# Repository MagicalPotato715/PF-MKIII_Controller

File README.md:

****PF-MKIII_Controller****
-----

About: This is the handheld controller for the third-generation of my hexapod project: Pathfinder. This controller features left and right hall effect joysticks - for rotation and movement, respectively. There are also three latch buttons for ON/OFF control of autonomous movement, the hexapod, and the controller itself - alongside numerous miscellaneous status LEDs. Additionally, to communicate with the hexapod, the controller uses an NRF Chip as the main transmitter and an Arduino ESP32 Nano as the MCU. 
---

Why: Pathfinder MK-III itself has an NRF transmitter onboard. Since it's supposed to operate with Inverse Kinematics (live movement), the only options for controls are to either set up a wifi connection with a computer or through a controller. Since the hexapod's MCU, the STM32-f446re, doesn't support wireless code uploading, the only option is through a controller.
---

Bill Of Materials
-----
|Component|Quantity|Model|Lowest Price|Link|
|---|---|---|---|---|
|Dev Board|1|Arduino ESP32 Nano|$11.79|[Link](https://www.aliexpress.com/item/3256807939051766.html?spm=a2g0o.cart.0.0.725738daz9Ksmg&mp=1&pdp_npi=5%40dis%21USD%21USD%2020.26%21USD%2012.56%21%21USD%2012.56%21%21%21%40210156fc17536786169312567e890e%2112000043892831353%21ct%21US%216187826129%21%211%210)|
|Battery|1|3.7v lipo|$5.16|[Link](https://www.aliexpress.com/item/3256808941846105.html?spm=a2g0o.cart.0.0.725738daz9Ksmg&mp=1&pdp_npi=5%40dis%21USD%21USD%205.16%21USD%205.16%21%21USD%205.16%21%21%21%400b1bf20817536788724595407e3676%2112000048014338867%21ct%21US%216187826129%21%211%210)|
|Joysticks|2 (1x5pcs)|09032|$5.3|[Link](https://www.aliexpress.com/item/3256808542713532.html?spm=a2g0o.cart.0.0.725738daz9Ksmg&mp=1&pdp_npi=5%40dis%21USD%21USD%2010.98%21USD%205.38%21%21USD%205.38%21%21%21%400b1bf20817536788724595407e3676%2112000046421716696%21ct%21US%216187826129%21%211%210)|
|NRF Transmitter|1|NRF24L01+|$2.30|[Link](https://www.aliexpress.com/item/3256805495903750.html?spm=a2g0o.productlist.main.2.6555405a81EXOg&algo_pvid=4da61190-12b2-4f13-9f49-e5557cba752b&algo_exp_id=4da61190-12b2-4f13-9f49-e5557cba752b-1&pdp_ext_f=%7B%22order%22%3A%222066%22%2C%22eval%22%3A%221%22%7D&pdp_npi=4%40dis%21USD%211.37%211.37%21%21%219.77%219.77%21%40212a6e2917536789864826848eb8be%2112000033996194288%21sea%21US%216187826129%21X&curPageLogUid=BgwmNtiZJQbL&utparam-url=scene%3Asearch%7Cquery_from%3A)|
|Latch Button|3 (1x10pcs)|6Pin Push Tactile|$1.29|[Link](https://www.aliexpress.com/item/2255800510764155.html?spm=a2g0o.cart.0.0.79d738daWxrOFF&mp=1&pdp_npi=5%40dis%21USD%21USD%201.29%21USD%201.29%21%21USD%201.29%21%21%21%40212a70c117536791531033590e52c9%2110000006101802626%21ct%21US%216187826129%21%211%210)|
|OLED Screen|1|SSD1306|$2.05|[Link](https://www.aliexpress.com/item/3256805954920554.html?spm=a2g0o.cart.0.0.79d738daWxrOFF&mp=1&pdp_npi=5%40dis%21USD%21USD%202.05%21USD%202.05%21%21USD%202.05%21%21%21%40212a70c117536791531033590e52c9%2112000035944225408%21ct%21US%216187826129%21%211%210)|
|Button|1|PBS-33B-G-X|$3.19|[Link](https://www.aliexpress.com/item/3256807265866776.html?spm=a2g0o.cart.0.0.79d738daWxrOFF&mp=1&pdp_npi=5%40dis%21USD%21USD%203.19%21USD%203.19%21%21USD%203.19%21%21%21%40212a70c117536791531033590e52c9%2112000040814174970%21ct%21US%216187826129%21%211%210)|
|RGB LED|2 (1x50pcs)|Common Cathode|$2.40|[Link](https://www.aliexpress.com/item/3256807678016250.html?spm=a2g0o.cart.0.0.79d738daWxrOFF&mp=1&pdp_npi=5%40dis%21USD%21USD%203.63%21USD%202.40%21%21USD%202.40%21%21%21%40212a70c117536791531033590e52c9%2112000042596159855%21ct%21US%216187826129%21%211%210)|
|Resistor Pack|1|510R, 44.7KR|$5.61|[Link](https://www.aliexpress.com/item/3256807883956541.html?spm=a2g0o.productlist.main.2.143211f2uS3ioA&algo_pvid=a85366f6-d296-4a62-9b70-adf952553cac&algo_exp_id=a85366f6-d296-4a62-9b70-adf952553cac-1&pdp_ext_f=%7B%22order%22%3A%22258%22%2C%22eval%22%3A%221%22%7D&pdp_npi=4%40dis%21USD%218.38%215.61%21%21%2159.73%2140.00%21%40213ba0c517536799111818556ea347%2112000043532036113%21sea%21US%216187826129%21X&curPageLogUid=7XvXStSYsJtD&utparam-url=scene%3Asearch%7Cquery_from%3A#nav-specification)|
|10uF Capacitor|1|0805W106K250CC|$0.6|[Link](https://www.aliexpress.com/item/1626652703.html?spm=a2g0o.productlist.main.1.48fb6316RMeZBk&algo_pvid=e693861e-0391-4f51-8de6-32cd16f941e8&algo_exp_id=e693861e-0391-4f51-8de6-32cd16f941e8-0&pdp_ext_f=%7B%22order%22%3A%22290%22%2C%22eval%22%3A%221%22%7D&pdp_npi=4%40dis%21USD%210.60%210.60%21%21%210.60%210.60%21%402102f22c17525900041745529e7ed1%2165044401121%21sea%21TW%216187826129%21ABX&curPageLogUid=cULtsx9Twjzu&utparam-url=scene%3Asearch%7Cquery_from%3A)|
|0.1uF Capacitor|2 (1x100pcs)|0603B104K250SD|$0.95|[Link](https://www.aliexpress.com/item/1005003512666695.html?spm=a2g0o.productlist.main.2.bb674964zgo3zW&aem_p4p_detail=202507151825544677393916540000689187&algo_pvid=30290dc5-6cab-4384-9250-c0f4dd7da1ce&algo_exp_id=30290dc5-6cab-4384-9250-c0f4dd7da1ce-1&pdp_ext_f=%7B%22order%22%3A%2266%22%2C%22eval%22%3A%221%22%7D&pdp_npi=4%40dis%21USD%210.95%210.95%21%21%210.95%210.95%21%400b1bf20a17526291538932348e9ac6%2112000026122537038%21sea%21TW%216187826129%21ABX&curPageLogUid=3zYrgz8WWygI&utparam-url=scene%3Asearch%7Cquery_from%3A&search_p4p_id=202507151825544677393916540000689187_1)|
|LED|2 (1x50pcs)|Green|$1.49|[Link](https://www.aliexpress.com/item/3256806082739727.html?spm=a2g0o.productlist.main.20.58265d61KYx3M3&algo_pvid=2888cd1a-db46-49cb-bcd1-dad9a1187035&algo_exp_id=2888cd1a-db46-49cb-bcd1-dad9a1187035-17&pdp_ext_f=%7B%22order%22%3A%22253%22%2C%22eval%22%3A%221%22%7D&pdp_npi=4%40dis%21USD%212.66%211.76%21%21%2118.96%2112.51%21%402102f22c17536801089633238e9268%2112000036543284014%21sea%21US%216187826129%21X&curPageLogUid=MgZMrUkmbKE4&utparam-url=scene%3Asearch%7Cquery_from%3A)|
|PCB|1||$41.41|JLCPCB Order|

Total Components Price: $61.50
PCB Price: $41.41
Total Price: $102.91

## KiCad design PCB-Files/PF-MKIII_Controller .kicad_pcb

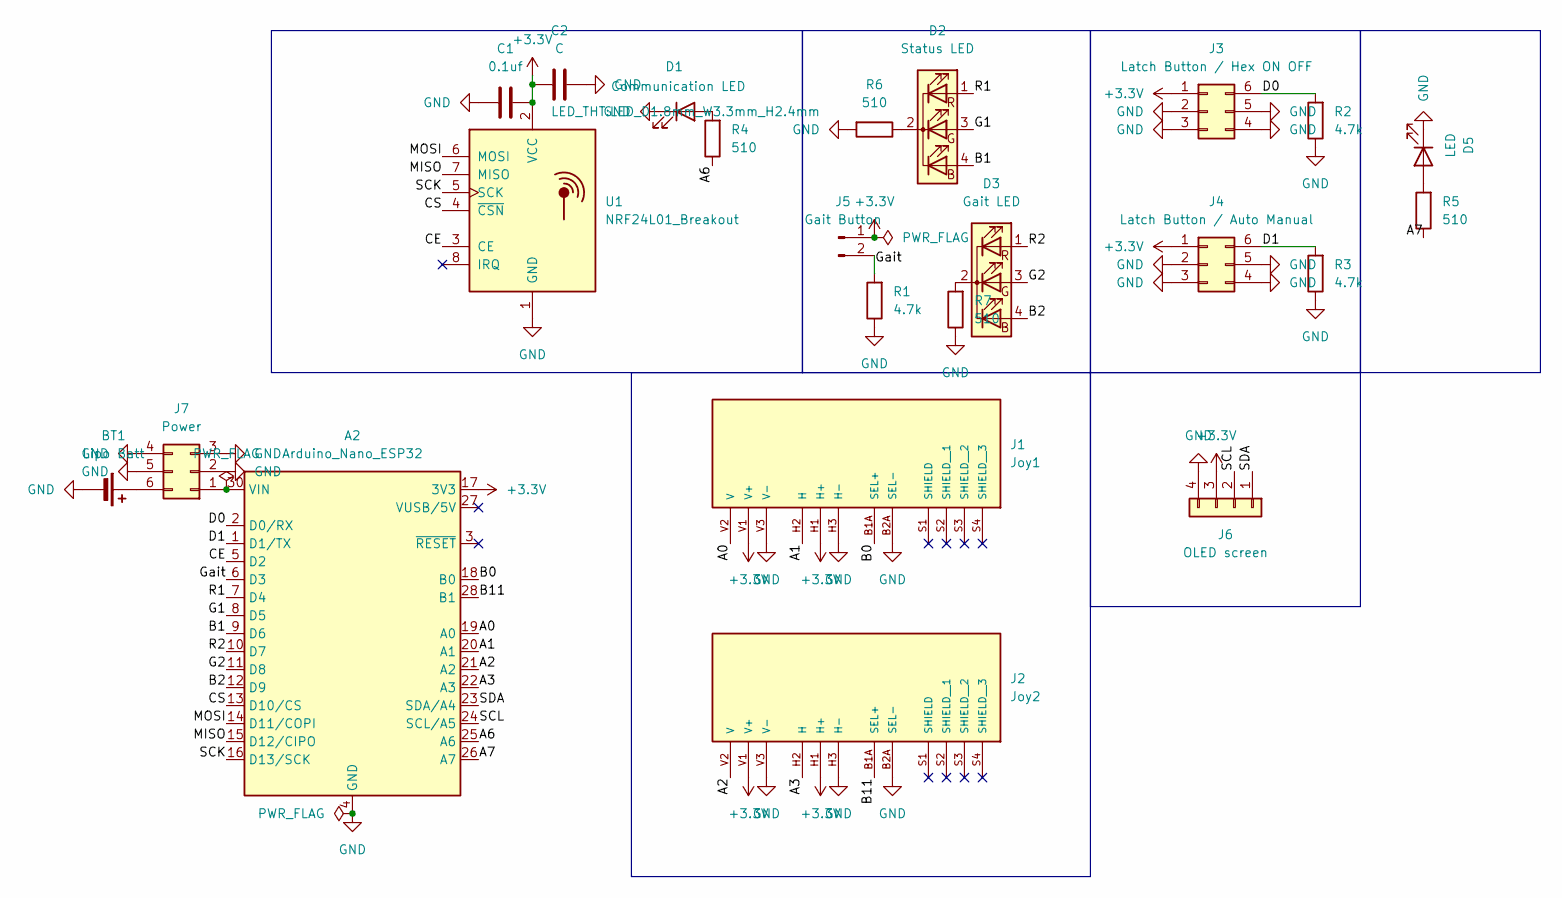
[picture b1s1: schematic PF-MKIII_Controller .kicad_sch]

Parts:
A2: Arduino_Nano_ESP32; Arduino_Nano
BT1: Lipo Batt; JST_PH_B2B-PH-K_1x02_P2.00mm_Vertical
C1: 0.1uf; C_0603_1608Metric
C2: C; C_0805_2012Metric
D1: Communication LED; LED_D1.8mm_W3.3mm_H2.4mm
D2: Status LED; LED_D5.0mm-4_RGB
D3: Gait LED; LED_D5.0mm-4_RGB
D5: LED; LED_D1.8mm_W3.3mm_H2.4mm
J1: Joy1; XDCR_COM-09032; PARTREV N/A
J2: Joy2; XDCR_COM-09032; PARTREV N/A
J3: Latch Button / Hex ON OFF; SW_DPDT_XLX
J4: Latch Button / Auto Manual; SW_DPDT_XLX
J5: Gait Button; PinHeader_1x02_P1.00mm_Vertical
J6: OLED screen; SSD1306_0.96_Oled
J7: Power; SW_DPDT_XLX
R1, R2, R3: 4.7k; R_Axial_DIN0204_L3.6mm_D1.6mm_P7.62mm_Horizontal
R4, R5, R6, R7: 510; R_Axial_DIN0204_L3.6mm_D1.6mm_P7.62mm_Horizontal
U1: NRF24L01_Breakout; nRF24L01_Breakout

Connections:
+3.3V: A2.17 (3V3), C1.2, C2.1, J1.H1 (H+), J1.V1 (V+), J2.H1 (H+), J2.V1 (V+), J3.1, J4.1, J5.1, J6.3, U1.2 (VCC)
/A0: A2.19 (A0), J1.V2 (V)
/A1: A2.20 (A1), J1.H2 (H)
/A2: A2.21 (A2), J2.V2 (V)
/A3: A2.22 (A3), J2.H2 (H)
/A6: A2.25 (A6), R4.1
/A7: A2.26 (A7), R5.1
/B0: A2.18 (B0), J1.B1A (SEL+)
/B1: A2.9 (D6), D2.4 (BA)
/B2: A2.12 (D9), D3.4 (BA)
/B11: A2.28 (B1), J2.B1A (SEL+)
/CE: A2.5 (D2), U1.3 (CE)
/CS: A2.13 (D10/CS), U1.4 (~CSN)
/D0: A2.2 (D0/RX), J3.6, R2.2
/D1: A2.1 (D1/TX), J4.6, R3.2
/G1: A2.8 (D5), D2.3 (GA)
/G2: A2.11 (D8), D3.3 (GA)
/Gait: A2.6 (D3), J5.2, R1.2
/MISO: A2.15 (D12/CIPO), U1.7 (MISO)
/MOSI: A2.14 (D11/COPI), U1.6 (MOSI)
/R1: A2.7 (D4), D2.1 (RA)
/R2: A2.10 (D7), D3.1 (RA)
/SCK: A2.16 (D13/SCK), U1.5 (SCK)
/SCL: A2.24 (SCL/A5), J6.2
/SDA: A2.23 (SDA/A4), J6.1
GND: A2.4 (GND), A2.29 (GND), BT1.2 (-), C1.1, C2.2, D1.1 (K), D5.1 (K), J1.B2A (SEL-), J1.H3 (H-), J1.V3 (V-), J2.B2A (SEL-), J2.H3 (H-), J2.V3 (V-), J3.2, J3.3, J3.4, J3.5, J4.2, J4.3, J4.4, J4.5, J6.4, J7.2, J7.3, J7.4, J7.5, R1.1, R2.1, R3.1, R6.2, R7.1, U1.1 (GND)
unnamed: A2.30 (VIN), J7.1
unnamed: BT1.1 (+), J7.6
unnamed: D1.2 (A), R4.2
unnamed: D2.2 (K), R6.1
unnamed: D3.2 (K), R7.2
unnamed: D5.2 (A), R5.2

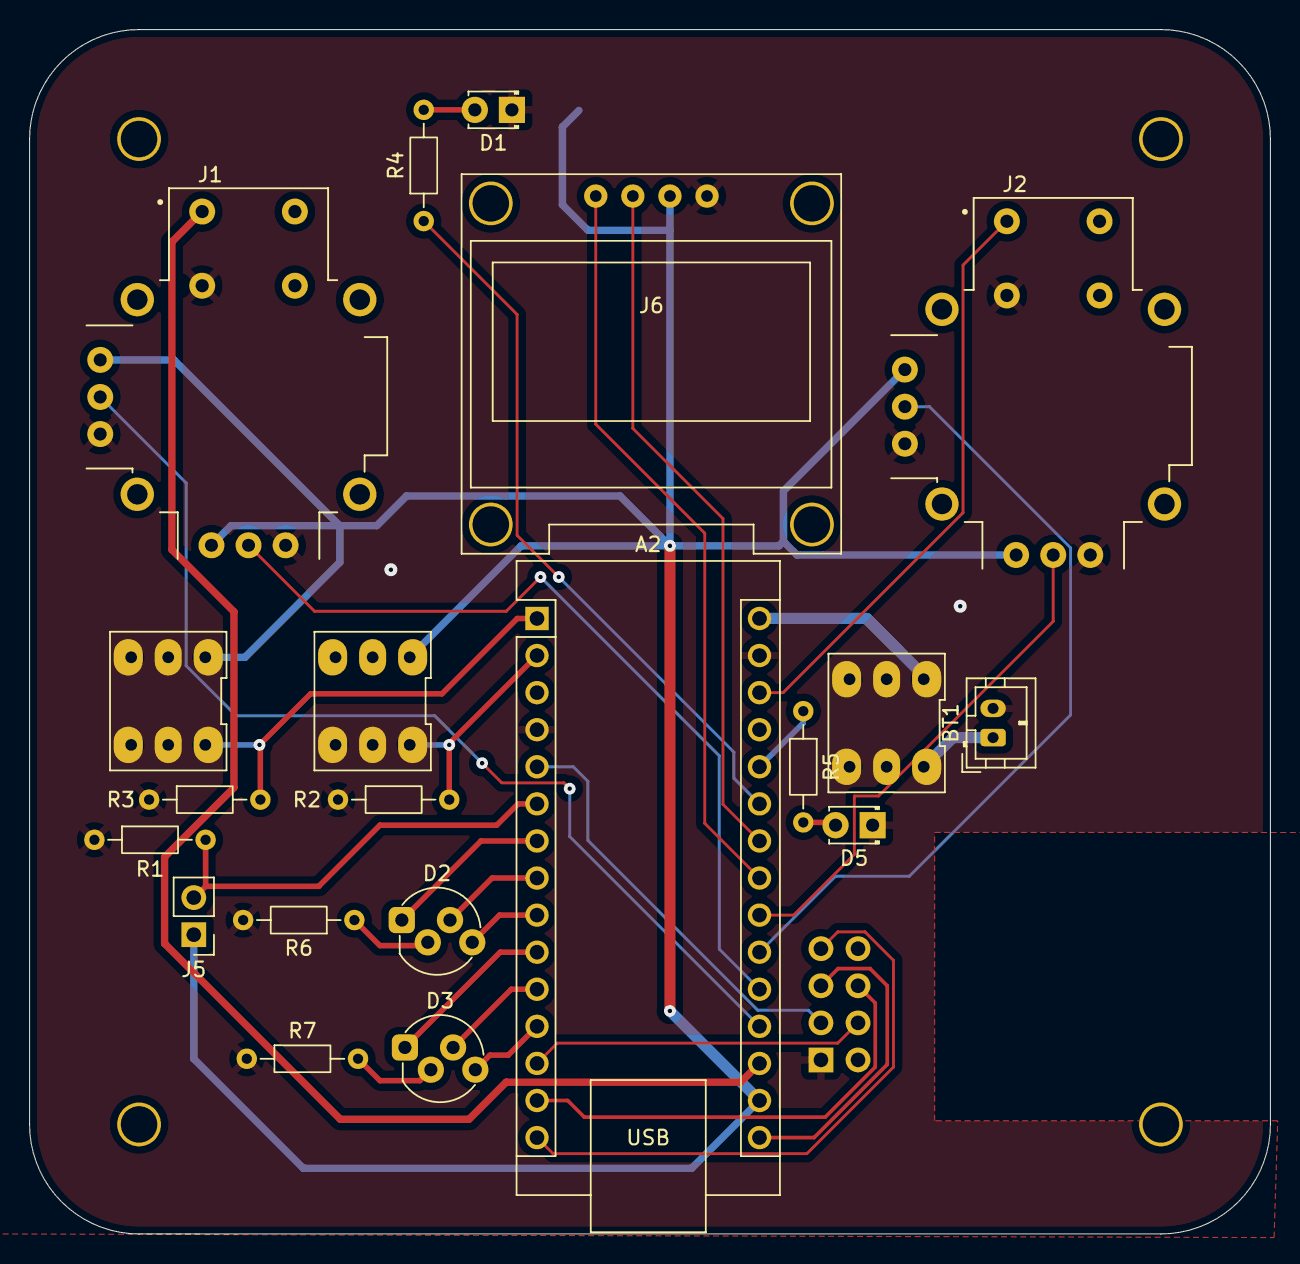
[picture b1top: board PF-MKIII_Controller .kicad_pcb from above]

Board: 2 copper layers, 85.0 x 82.5 mm, 21 parts (1 on the bottom side), 32 nets.

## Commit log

2025-07-28 Create a
2025-07-28 Rename PF-MKIII_Controller .pdf to Schematic.pdf
2025-07-28 Create l
2025-07-28 Create o
